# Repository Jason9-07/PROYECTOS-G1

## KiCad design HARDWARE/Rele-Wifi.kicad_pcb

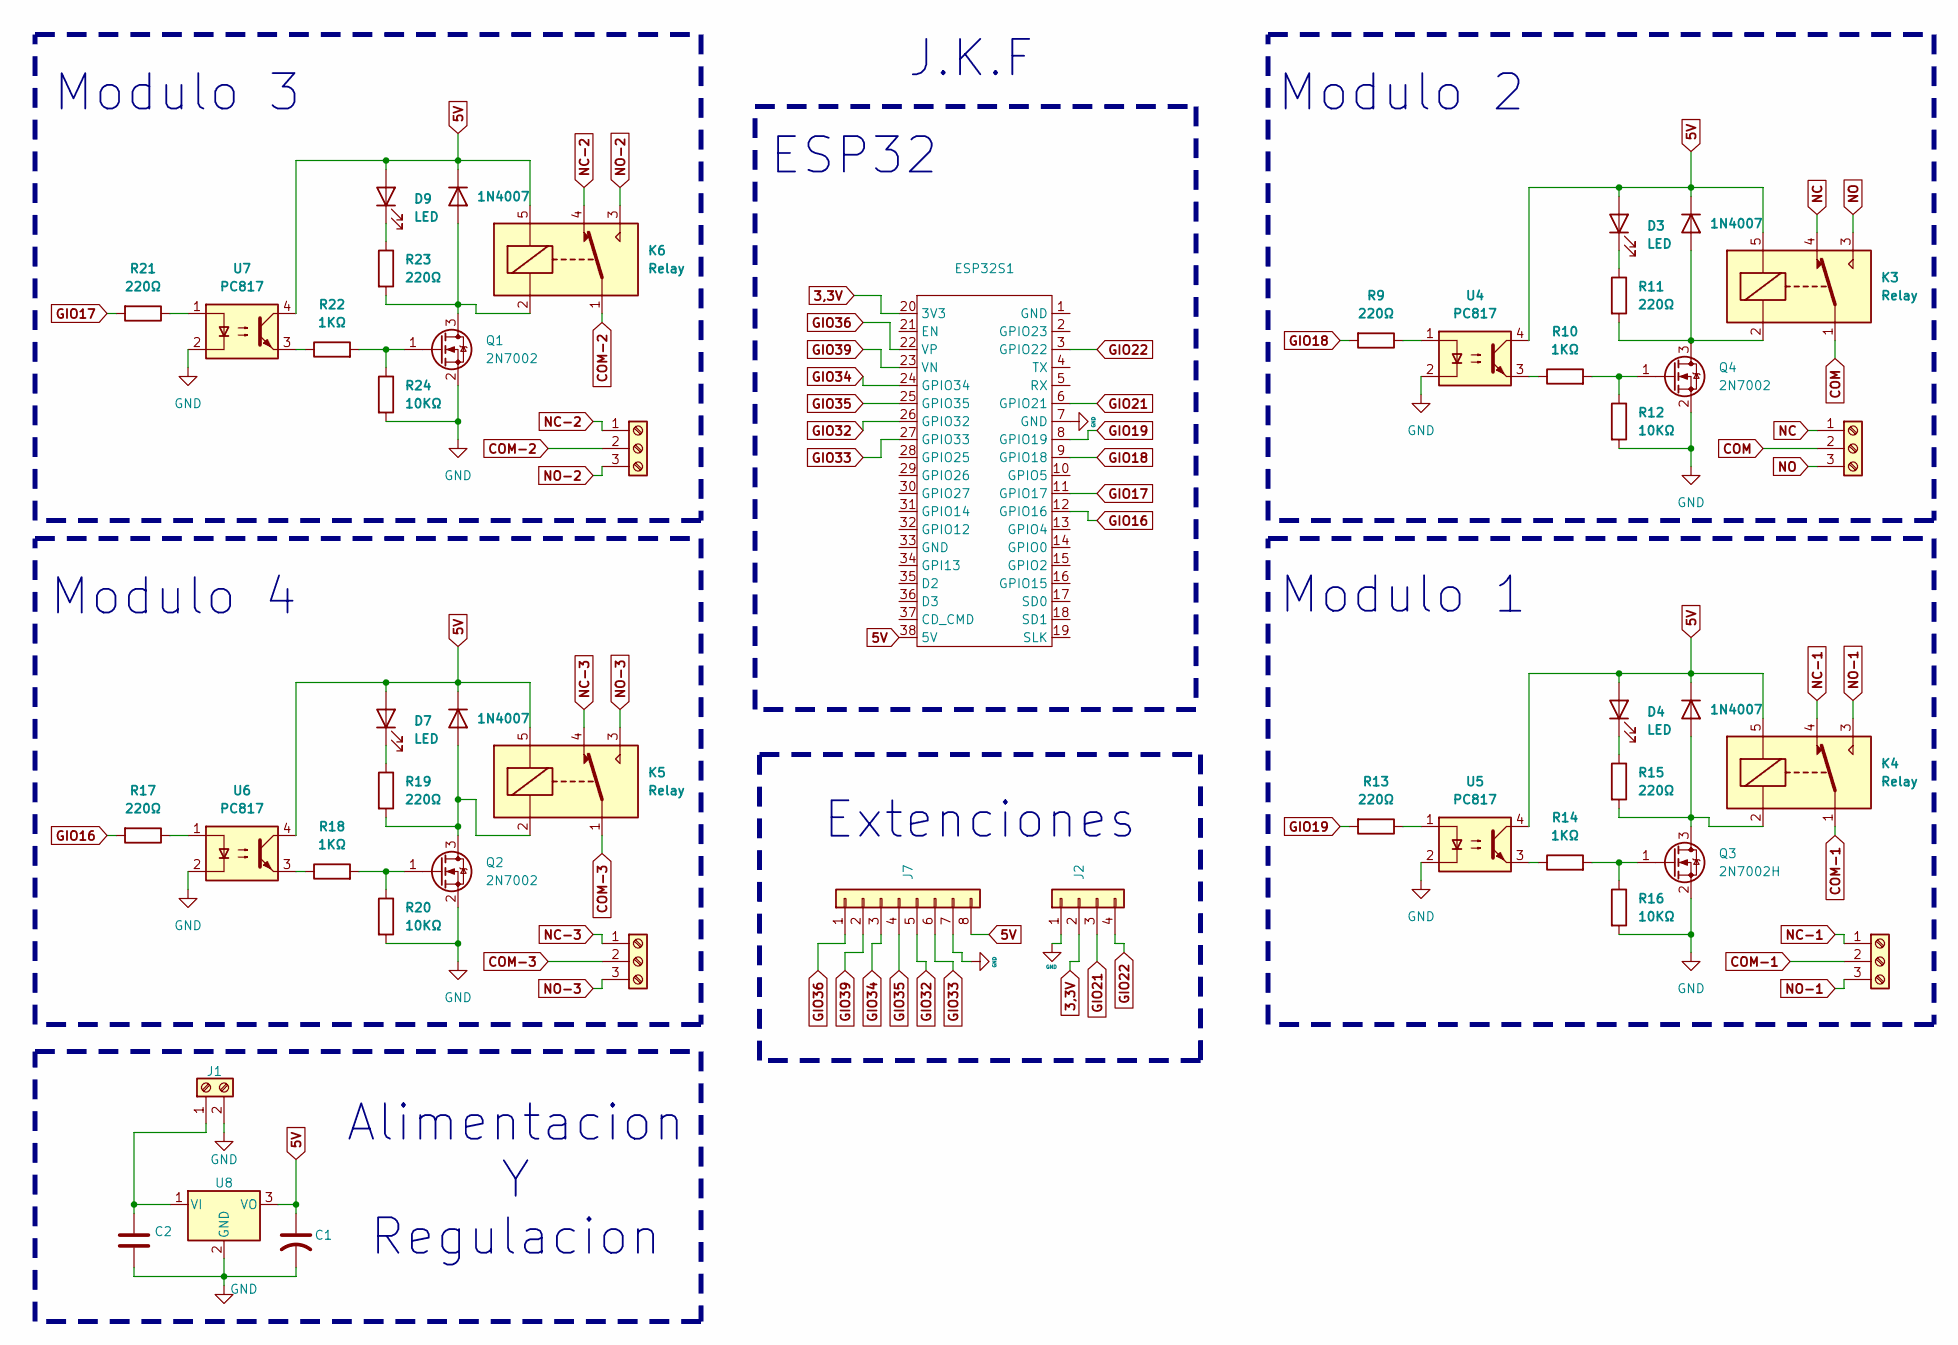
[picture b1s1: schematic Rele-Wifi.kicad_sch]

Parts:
C1: C_US; C_0805_2012Metric
C2: C; C_0805_2012Metric
D3, D4, D7, D9: LED; LED_0805_2012Metric
D5, D6, D8, D10: 1N4007; D_SMA
ESP32S1: ESP32S_38_PINES
J1: Screw_Terminal_01x02; TerminalBlock_MaiXu_MX126-5.0-02P_1x02_P5.00mm
J2: Conn_01x04; PinSocket_1x05_P2.54mm_Vertical
J3, J4, J5, J6: Screw_Terminal_01x03; TerminalBlock_MaiXu_MX126-5.0-03P_1x03_P5.00mm
J7: Conn_01x08; PinSocket_1x08_P2.54mm_Vertical
K3, K4, K5, K6: Relay; Relay_SPDT_SANYOU_SRD_Series_Form_C
Q1, Q2, Q4: 2N7002; SOT-23
Q3: 2N7002H; SOT-23
R9, R11, R13, R15, R17, R19, R21, R23: 220Ω; R_0805_2012Metric
R10, R14, R18, R22: 1KΩ; R_0805_2012Metric
R12, R16, R20, R24: 10KΩ; R_0805_2012Metric
U4, U5, U6, U7: PC817; DIP-4_W7.62mm
U8: KA78M05_TO252; TO-263-2

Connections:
3,3V: ESP32S1.20 (3V3), J2.2
5V: C1.1, D3.2 (A), D4.2 (A), D5.1 (K), D6.1 (K), D7.2 (A), D8.1 (K), D9.2 (A), D10.1 (K), ESP32S1.38 (5V), J7.8, K3.5, K4.5, K5.5, K6.5, U4.4, U5.4, U6.4, U7.4, U8.3 (VO)
COM: J3.2, K3.1
COM-1: J4.2, K4.1
COM-2: J6.2, K6.1
COM-3: J5.2, K5.1
GIO16: ESP32S1.12 (GPIO16), R17.2
GIO17: ESP32S1.11 (GPIO17), R21.2
GIO18: ESP32S1.9 (GPIO18), R9.2
GIO19: ESP32S1.8 (GPIO19), R13.2
GIO21: ESP32S1.6 (GPIO21), J2.3
GIO22: ESP32S1.3 (GPIO22), J2.4
GIO32: ESP32S1.26 (GPIO32), J7.5
GIO33: ESP32S1.27 (GPIO33), J7.6
GIO34: ESP32S1.24 (GPIO34), J7.3
GIO35: ESP32S1.25 (GPIO35), J7.4
GIO36: ESP32S1.22 (VP), J7.1
GIO39: ESP32S1.23 (VN), J7.2
GND: C1.2, C2.2, ESP32S1.7 (GND), J1.2, J2.1, J7.7, Q1.2 (S), Q2.2 (S), Q3.2 (S), Q4.2 (S), R12.2, R16.2, R20.2, R24.2, U4.2, U5.2, U6.2, U7.2, U8.2 (GND)
NC: J3.1, K3.4
NC-1: J4.1, K4.4
NC-2: J6.1, K6.4
NC-3: J5.1, K5.4
NO: J3.3, K3.3
NO-1: J4.3, K4.3
NO-2: J6.3, K6.3
NO-3: J5.3, K5.3
unnamed: D3.1 (K), R11.1
unnamed: D4.1 (K), R15.1
unnamed: D5.2 (A), K3.2, Q4.3 (D), R11.2
unnamed: D6.2 (A), K4.2, Q3.3 (D), R15.2
unnamed: D7.1 (K), R19.1
unnamed: D8.2 (A), K5.2, Q2.3 (D), R19.2
unnamed: D9.1 (K), R23.1
unnamed: D10.2 (A), K6.2, Q1.3 (D), R23.2
unnamed: C2.1, J1.1, U8.1 (VI)
unnamed: Q1.1 (G), R22.2, R24.1
unnamed: Q2.1 (G), R18.2, R20.1
unnamed: Q3.1 (G), R14.2, R16.1
unnamed: Q4.1 (G), R10.2, R12.1
unnamed: R9.1, U4.1
unnamed: R10.1, U4.3
unnamed: R13.1, U5.1
unnamed: R14.1, U5.3
unnamed: R17.1, U6.1
unnamed: R18.1, U6.3
unnamed: R21.1, U7.1
unnamed: R22.1, U7.3

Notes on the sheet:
ESP32
Modulo 1
Extenciones
Modulo 2
J.K.F
Alimentacion Y Regulacion
Modulo 4
Modulo 3

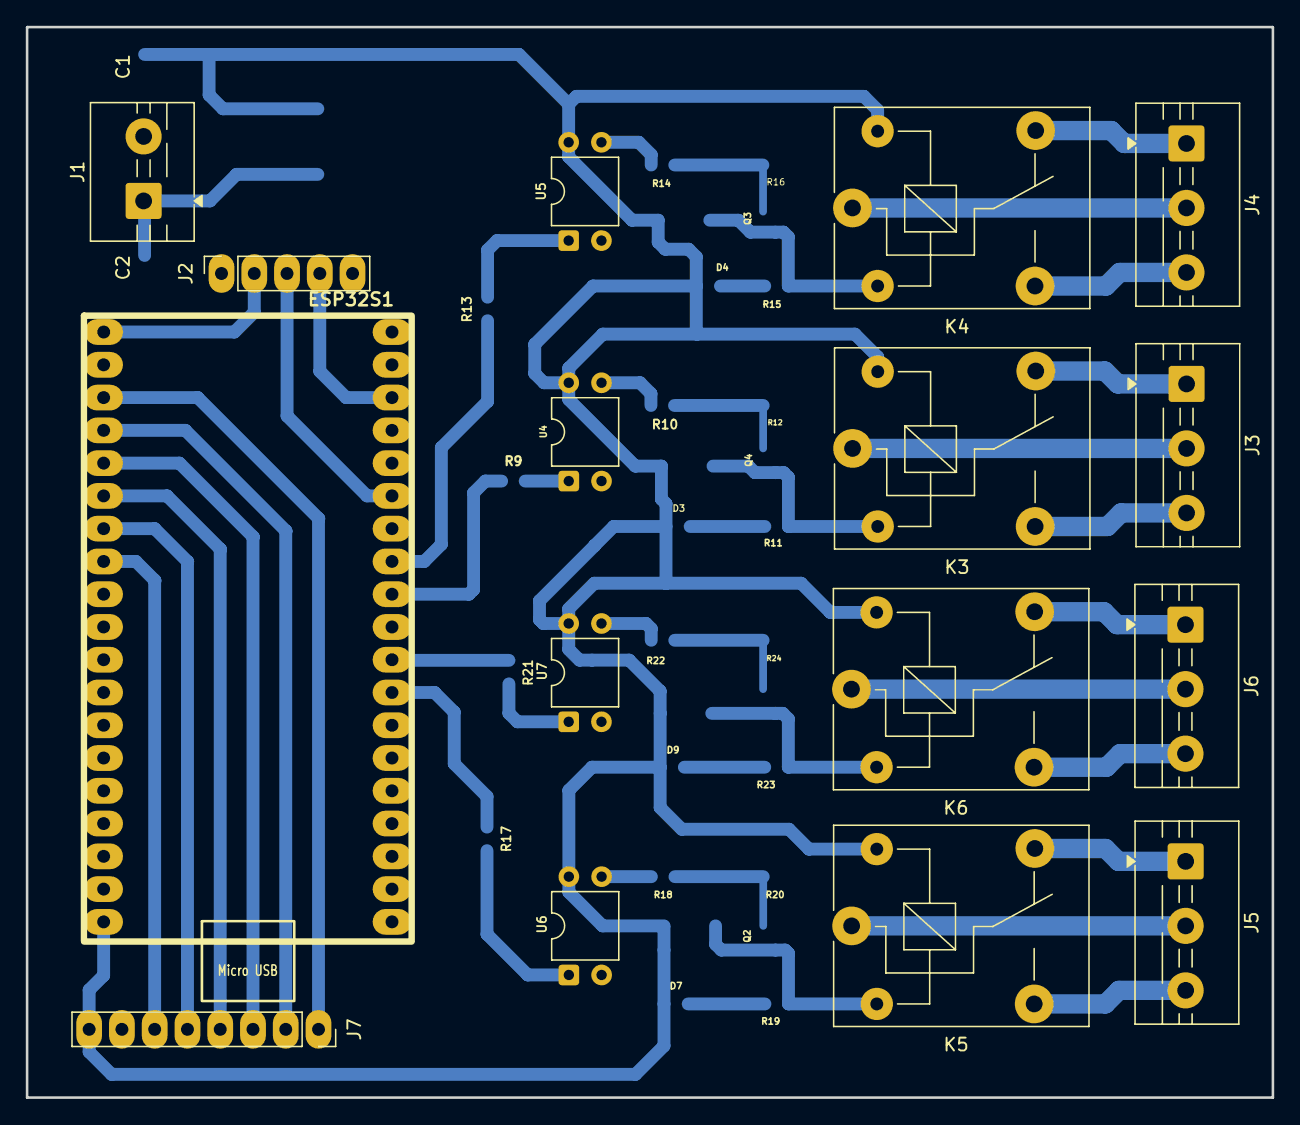
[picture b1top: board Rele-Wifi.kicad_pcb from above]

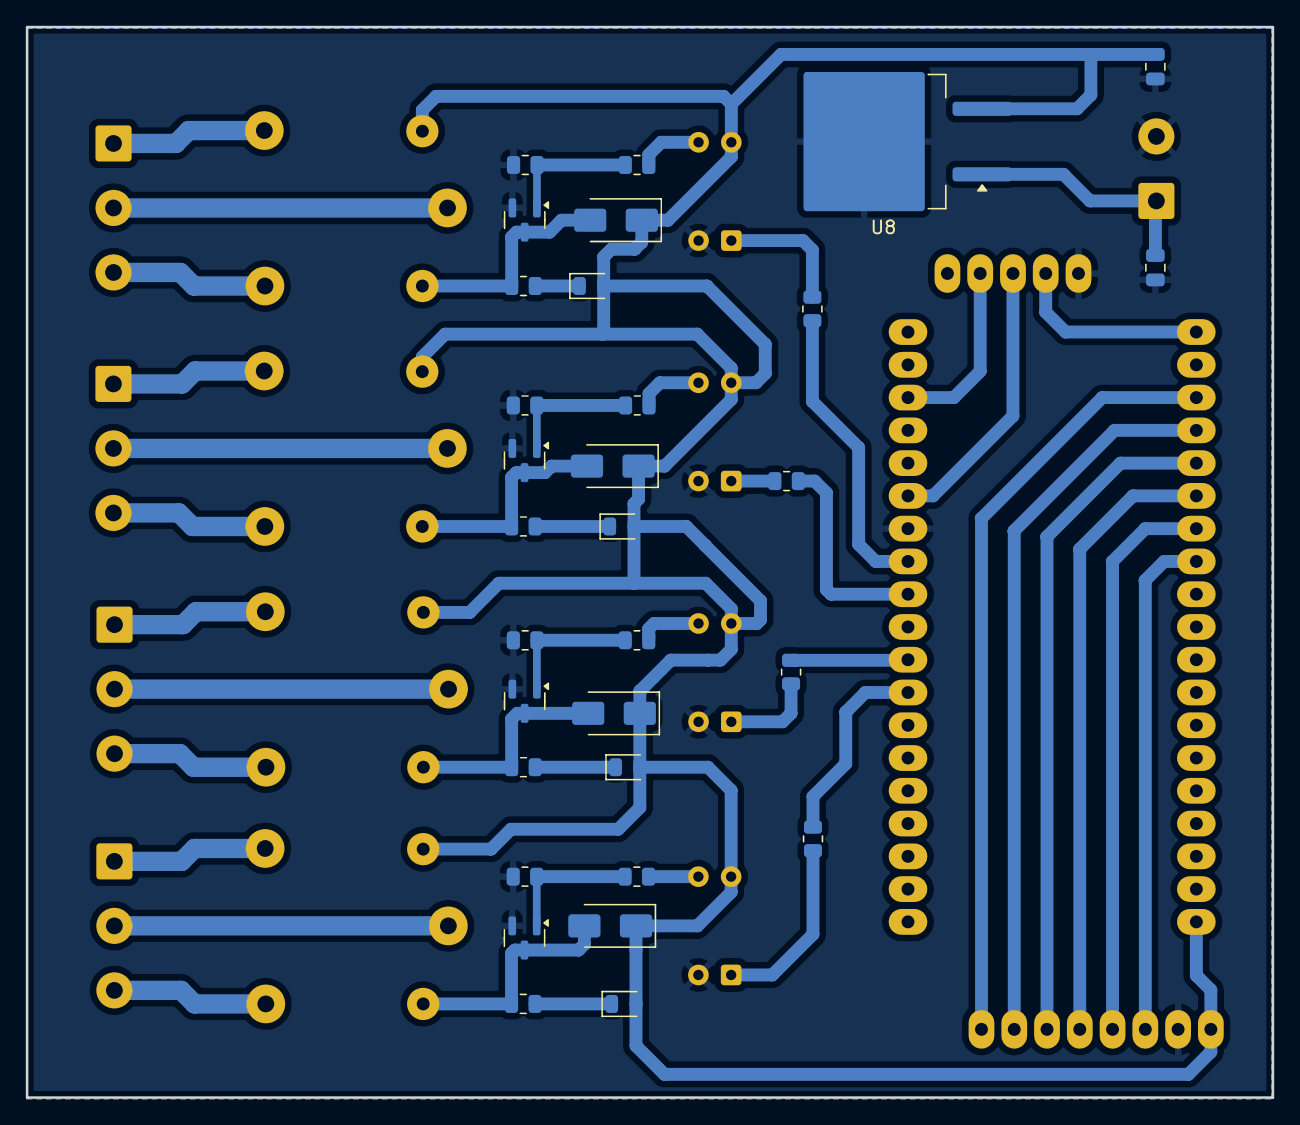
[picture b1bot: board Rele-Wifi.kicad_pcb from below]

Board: 2 copper layers, 96.6 x 83.0 mm, 47 parts (31 on the bottom side), 48 nets.

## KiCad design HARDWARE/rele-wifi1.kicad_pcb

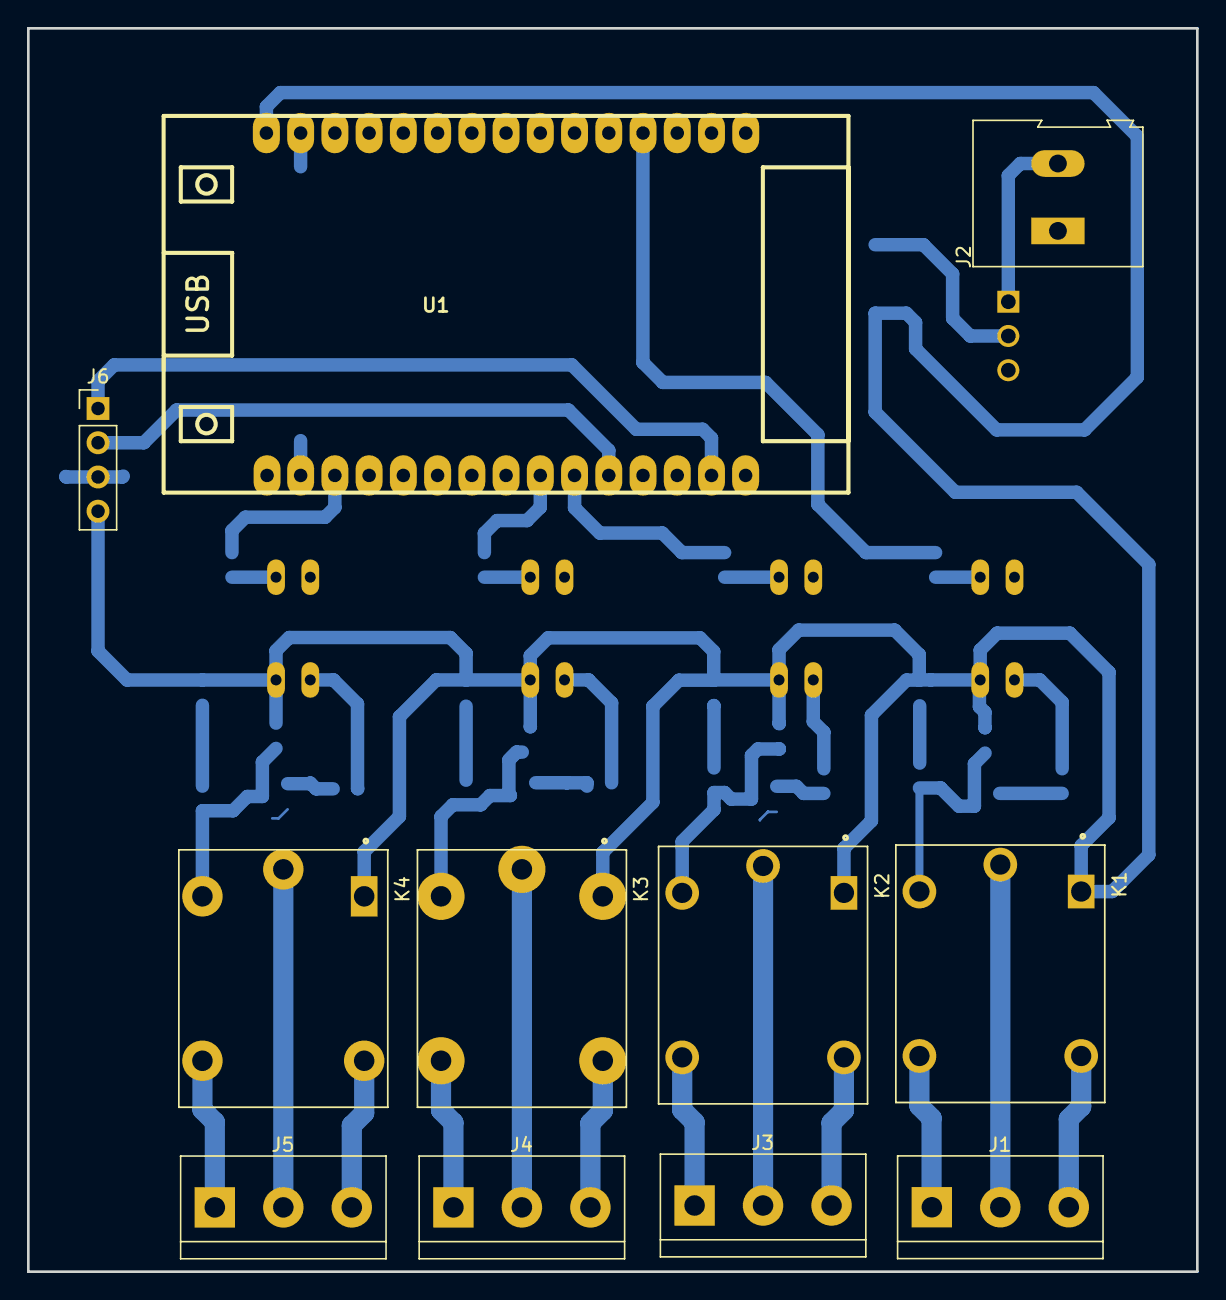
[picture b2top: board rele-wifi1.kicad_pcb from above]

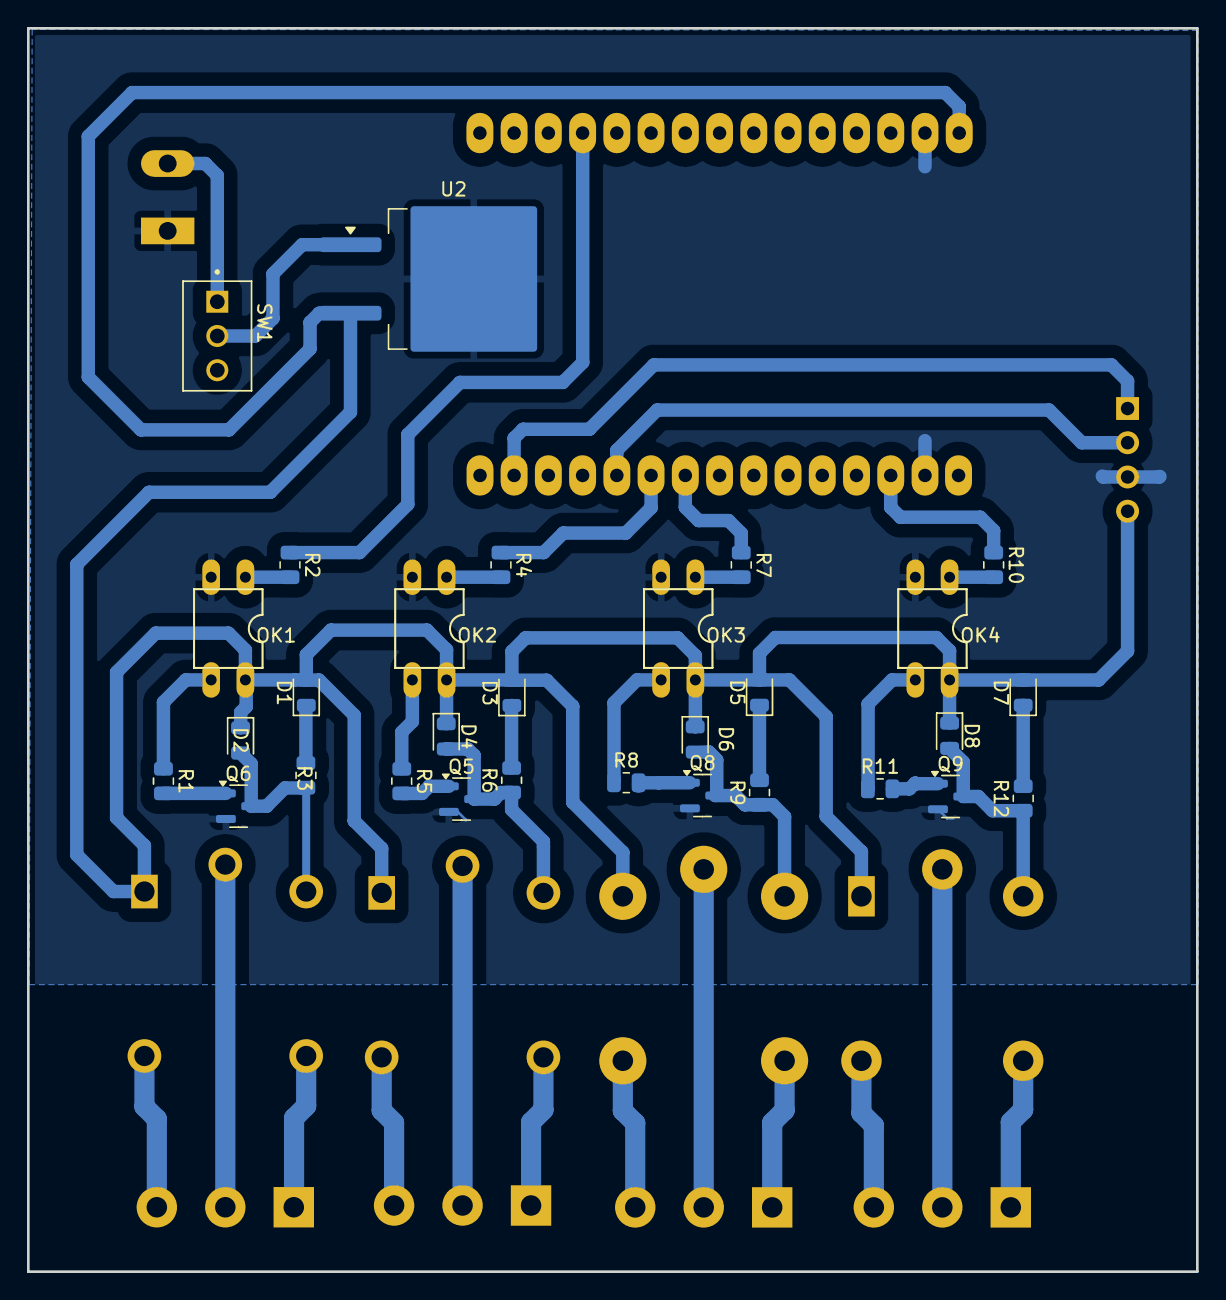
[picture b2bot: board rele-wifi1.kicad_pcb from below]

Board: 2 copper layers, 86.7 x 92.2 mm, 41 parts (30 on the bottom side), 42 nets.

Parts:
D1, D3, D5, D7: LED; LED_0805_2012Metric
D2, D4, D6, D8: 1N4007; D_0805_2012Metric
J1, J3, J4, J5: Screw_Terminal_01x03; TerminalBlock_bornier-3_P5.08mm
J2: ENTRADA; TerminalBlock_Altech_AK300-2_P5.00mm
J6: Conn_01x04; PinHeader_1x04_P2.54mm_Vertical
K1, K2, K3, K4: SRD-05VDC-SL-C; RELAY_SRD-05VDC-SL-C
OK1, OK2, OK3, OK4: PC814; DIL04
Q5, Q6, Q8, Q9: MMBT2222A; SOT-23
R1, R5, R8, R11: 1K; R_0805_2012Metric
R2, R3, R4, R6, R7, R9, R10, R12: 220R; R_0805_2012Metric
SW1: SW_DPST_x2; SW_2MS1T1B1M2QES-5
U1: ESP32_DevKit_V1_CH9102X
U2: L7805; TO-263-2

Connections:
+5V: D1.2 (A), D2.1 (K), D3.2 (A), D4.1 (K), D5.2 (A), D6.1 (K), D7.2 (A), D8.1 (K), J6.4, K1.A1, K2.A1, K3.A1, K4.A1, OK1.4, OK2.4, OK3.4, OK4.4, U1.15 (VIN), U2.3 (OUT)
COM: J1.2, K1.COM
COM1: J3.2, K2.COM
COM2: J4.2, K3.COM
COM3: J5.2, K4.COM
D21: J6.2, U1.20 (D21)
D22: J6.1, U1.17 (D22)
GND: J2.1, J6.3, OK1.2, OK2.2, OK3.2, OK4.2, Q5.2 (E), Q6.2 (E), Q8.2 (E), Q9.2 (E), U1.14 (GND), U1.29 (GND), U2.2 (GND)
INPUT: R2.1, U1.4 (D34)
INPUT1: R4.1, U1.21 (D19)
INPUT2: R7.1, U1.22 (D18)
INPUT3: R10.1, U1.28 (D15)
NC: J1.3, K1.NC
NC1: J3.3, K2.NC
NC2: J4.3, K3.NC
NC3: J5.3, K4.NC
NO: J1.1, K1.NO
NO1: J3.1, K2.NO
NO2: J4.1, K3.NO
NO3: J5.1, K4.NO
unnamed: D1.1 (K), R3.2
unnamed: D2.2 (A), K1.A2, Q6.3 (C), R3.1
unnamed: D3.1 (K), R6.2
unnamed: D4.2 (A), K2.A2, Q5.3 (C), R6.1
unnamed: D5.1 (K), R9.2
unnamed: D6.2 (A), K3.A2, Q8.3 (C), R9.1
unnamed: D7.1 (K), R12.2
unnamed: D8.2 (A), K4.A2, Q9.3 (C), R12.1
unnamed: J2.2, SW1.1 (A)
unnamed: OK1.1, R2.2
unnamed: OK1.3, R1.1
unnamed: OK2.1, R4.2
unnamed: OK2.3, R5.1
unnamed: OK3.1, R7.2
unnamed: OK3.3, R8.1
unnamed: OK4.1, R10.2
unnamed: OK4.3, R11.1
unnamed: Q5.1 (B), R5.2
unnamed: Q6.1 (B), R1.2
unnamed: Q8.1 (B), R8.2
unnamed: Q9.1 (B), R11.2
unnamed: SW1.2 (B), U2.1 (IN)

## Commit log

2025-05-07 Crear carpeta HARDWARE
2025-05-07 Crear carpeta SOFTWARE
2025-05-07 Crear carpeta 3D
2025-06-04 rele-wifi README.md.
    Correcion del pcb
2025-06-04 las quintillisas
    pcb corregido
2025-06-11 2,0
    pcb terminado
2025-06-18 corregido
    corregimos lo que faltaba
2025-06-18 3.0
    end
2025-09-24 7805 nueva
    EL 7805 SE CAMBIO LA HUELLA
2025-09-24 TRABAJO FINAL
2025-09-24 trabajo final2
2025-09-24 CAMBIO DE HUELLA
2025-10-21 end
    placa finalizada
2025-10-21 pcb terminado
    el pcb ya terminado
